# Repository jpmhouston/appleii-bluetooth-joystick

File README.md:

> [!WARNING]
> I'm not really a hardware guy, so there might be stupid stuff here. I assume no liability for you using this with your Apple II. Damage could occur both to it and your ESP32 if I got anything wrong or if you wire it wrong. Build one at your own risk.
> Also, this was built for my Apple IIGS and Laser 128.  They use 9 pin DE9 connectors. You'll have to figure out how to do something different if you have the 15 pin connector.

---

---

# Purpose

My old school analog joystick isn't great so I wanted to buy a "new" one. But I discovered that even crappy period correct ones are like $50 on ebay. I'm cheap and I also have a bunch of modern gamepads around. So I thought, why not build something to allow those modern gamepads to work with my Apple IIGS and my Laser 128?

So this let's you use a modern bluetooth gamepad on an Apple II. I'll probably still buy a joystick, but this was a fun project anyway.

If you do anything with electronics then you probably have a hoard of parts on hand. This project is cheap in theory if you already have common parts like breadboards, resistors, diodes, etc. Most of the components are cheap, but they only come in bulk so you'll end up paying more if you don't already have some on hand. And digikey is great but shipping is $. All in all, depending on what you have hoarded way, it'll probably cost you somewhere between $15 and $35.

Note: I also saw you can buy an A2io. I'm sure it's better, but it was $55 and it looks like it requires using a mobile device. I didn't want to have to use a mobile app and really the fun was in building this.

# Credits

I learned about how the Apple II joysticks work primarily by reading my Laser 128 technical reference manual and [this article](https://blondihacks.com/apple-ii-gamepad-prototype/) by Quinn Dunki.

For the ESP32/bluetooth side, this project uses Bluepad32. Here are some links I found helpful.
* [Some Bluepad32 docs](https://gitlab.com/ricardoquesada/bluepad32/-/blob/main/docs/plat_arduino.md#1-add-esp32-and-bluepad32-board-packages-to-board-manager)
* [ESP-IDF + Arduino + Bluepad32 template app](https://github.com/ricardoquesada/esp-idf-arduino-bluepad32-template)

# Usage

## Connecting everything

Plug the DE9 into your joystick port. Plug your ESP32 into USB. They are powered separately. See the section below on power rails, but generally it should be fine to do this in either order. It's probably a good idea to do this with your Apple off.

## Pairing controllers

By default, bluepad32 pairing is automatic when devices are put in pairing mode. Instead, I implemented an on-device pairing mode so that you can ignore new controllers if you're trying to pair them with other devices in the area. To pair a new controller, you need to bring Pin 13 to low. You can do this with a physical switch or if you're using a breadboard just connect Pin 13 to ground.

If you have one controller connected, then connect another one, the second one will be the one used.

## Calibrating your controller

You may find that center on your joystick isn't center on the Apple II. See the section on how analog sticks work and you can probably guess why. Not to mention you may have decades old capacitors in your machine.

Pressing L1 and R1 simultaneously on your controller will capture an offset value for x and y and apply this to your joystick readings. This allows you to center the controller. If you have the TotalReplay image (google it), there's a joystick program you can use. You can move the stick until it's in the center and press L1 and R1.

The calibration is saved in flash memory so it will stick even when you remove power.

# How this stuff works if you want to build one

As mentioned in the warning at the top of this readme, I know just enough hardware stuff to get by. And not enough to get by in some cases. So if you're reading this and you see I'm wrong about something or did something dangerous, let me know! Especially if there's risk of damaging an Apple II! Better yet, contribute some code or modify the design if you have a better way.

## Analog sticks using digital potentiometers (used as rheostats)

Traditional Apple II analog joysticks were pretty simple. Inside are two 150k ohm potentiometers, one for each axis. As you move the stick, it adjusts the potentiometers (pots) and changes the resistance in a circuit on the Apple II. The computer measures how long it takes to charge an internal capacitor through that resistance. Because the charging time varies, it can detect fine movements and exact angles. This is pretty cool compared to digital joysticks like the C64 or Ataris used, which were simple on-off switches for four directions.

This project works by using digital potentiometers (digipots). It converts the position of the stick on your modern gamepad to resistance values for the digipots. The Apple II expects between 0 and 150kohms resistance but 150kohm resistors are hard to find. So this project uses two 100kohm digipots in series per axis.

If you want to make it cheaper, you can probably just use one 100kohm digipot per axis. You may lose some range, though. I haven't tried this, but it seems like that's what others have done when they've built physical joysticks, and the common complaint is that it may not work great for things like flight simulators.

The code basically sets the two MCP4161 digipots per axis to the same wiper values and wires them in series. E.g. to get 150kohms of resistance, both digipots are set to 75kohm.

Also, my oldschool joystick allowed close to a square movement pattern. My modern gamepads are pretty constrained to a circle. So the code "squares the circle" a bit to provide a more authentic response. You can control how much by tweaking the code. See the SQUARENESS value.

Finally, there are some variables you can set to control how low the wipers can go. Play with those if you want. See WIPER\\_MIN\_SAFE.

## Buttons

Apple II buttons are quite simple. We get the button state from bluepad32. When a button is not being pressed, we want the Apple II button switch input to float. When it's being pressed, we bring it to 5V through a 470 ohm resistor. We make use of a diode for this.

## Power rails

This project interfaces an ESP32 (3.3V logic) with an Apple II (5V logic). Because these devices operate at different voltages, some care was taken to ensure signal integrity and hardware safety. Again, I'm not an expert so please point out any flaws in the design.

## Level shifting, isolation, and fail-safe

All 3.3V SPI and control signals from the ESP32 are level-shifted through a 74HCT245 bus transceiver.
* The 74HCT245 is powered by the 5V rail from the Apple II Game I/O port.
* Note: The "T" variant (HCT) is used because its input threshold is compatible with 3.3V logic but it can output 5V for the Apple II and digipots.

To prevent backfeeding power or sending spurious SPI commands to the digipots when one system is off, the 74HCT245's OE pin is managed by a hardware failsafe.
* A 10K pullup resistor connects the OE pin to the Apple II 5V rail. So if the ESP32 is not connected or is powered down, OE is HIGH and the buffer is in a high impedance state.
* A 2N7000 MOSFET acts as an inverter. When the ESP32 GPIO pins initialize and drive the MOSFET Gate HIGH, the MOSFET pulls the OE pin to ground, enabling the outputs.

Note: The 2N7000 has a gate threshold that can range up to 3.0V. Since the ESP32 outputs 3.3V, there isn't much overhead for the transistor to turn fully on. This should still be sufficient for switching the OE pin, but your mileage may vary. To test, check the voltage at the OE pin. It should drop reasonably close to 0V when the ESP32 is active. A logic-level MOSFET with a lower gate threshold is probably better, but I had a ton of these on hand and it's working for me.

## Parts list

Here's what I used in building this device. It would probably be cheaper to make a PCB since a lot of the expense is breadboards/breakout boards, etc. Most of what I bought came in packs of a bunch, so it could be more expensive if you don't already have stuff on hand like resistors, diodes, etc.
* 1 - [ESP32](https://www.amazon.com/dp/B0D8T53CQ5?ref=ppx_yo2ov_dt_b_fed_asin_title) - $6.67 each. Make sure you get one that supports classic bluetooth mode. Look at bluepad32's docs above to make sure.
* 1 - [ESP32 breakout board](https://www.amazon.com/dp/B0BNQ85GF3?ref=ppx_yo2ov_dt_b_fed_asin_title&th=1) - $4.33 each. Not strictly necessary but made it a lot easier to mess around.
* 4 - [MCP4161-104E/P digipots](https://www.digikey.com/en/products/detail/microchip-technology/MCP4161-104E-P/1874169) - $1.38 each
* 1- [DB9 breakout board] (https://www.amazon.com/dp/B09L7JWNDQ?ref=ppx_yo2ov_dt_b_fed_asin_title&th=1) - $7.96. You can do this with a simple male connector if you want to save money. I just found it a lot easier to wire up this way.
* About 10 [104 capacitors] - about $0.70 total.
* 1- [74HCT245N](https://www.digikey.com/en/products/detail/texas-instruments/SN74HCT245N/277258) - $0.92 each.
* 2 - 1N5817 diodes
* 1 - [2N7000 MOSFET](https://www.amazon.com/dp/B0CBKHJQZF?ref=ppx_yo2ov_dt_b_fed_asin_title&th=1) - $0.08 each. 
* Resistors. Just get a kit if you don't already have any. You'll need 6x1kohm resistors, a couple of 10K resistors, a couple of 470ohm resistors.
* Wire and terminals depending on how you want to build it.
* Breadboard or a solderable board of some kind.. Get whatever you want. A good one's about $8.

## Layout

Check out the [schematic](./schematic/schematic.kicad_sch) built using [KiCad](https://www.kicad.org/). 

Notes:
* My ESP32 had different pin numbers than the drawing shows, so just make sure the right GPIO/IO lines are used rather than paying attention to the pin numbers listed.
* I also sprinkled some 0.1 µF ceramic capacitors (104s) along the power rails (VCC to GND). These aren't shown in the drawing.
* The Apple II calls for 470ohm resistors on the buttons. On my Laser 128, that kept me borderline on button presses. I DON'T RECOMMEND IT BECAUSE THE SPEC CALLS FOR 470 ohms and I'm paranoid. But if the buttons aren't triggering you could try a lower value resistor. Do this at your own risk.

# Next steps / Possible problems

It might be good to add some physical pots for the stick calibration. Some adjustments for min/max resistance and for centering. We could get much more precise calibrations that way and you wouldn't need to use a calibration program. You could also do it mid-game.

I noticed that when you have the stick all the way down and to the left, sometimes there's an overflow and the stick will jump to the top in the joystick calibration program. This also happens with my old school physical joystick so maybe it's just a practical hardware limitation.

I've never designed a PCB before, but I think this would be pretty cheap if someone wanted to give it a go. I'd go in on it with you if you want to build a bunch. I used through hole components since I suck at soldering and am scared to try doing SMDs.

---

# Addendum by jpmhouston ... Second draft of a PCB 🎉

This is made directly from the KiCad schematic, I haven't made a breadboard prototype yet. I'm a beginner at PCBs also, but started learning KiCad recently for another project.

I don't know much about the DE9 serial port connector and its mounting screws (called jackscrews?), but I moved some components around from the simply rectangular, first draft PCB and now there might be enough space for them (slightly more then 1cm).

Component Q3 is the one I didn't find a surface mount replacement for however there's more than enough vertical space for it compared to the DE9 connector which I placed it close to. I picked a push button for the pairing switch and placed it at the back. The only thinking I did about a case is guessing that it could be made shallow at the back to allow exposing this button.

I also don't know much about the ESP32 and guessed that the antenna part needs to be exposed off the board at the back, exposed though an eventual case.

This board design measures 34mm wide (just under 1 3/8") x 35.8mm deep (also roughly 1 1/2") not counting the antenna. I haven't yet, but I intended to make a mock up out of cardboard, see how this sizes up compared to real hardware (I have a //e here).

---

These are the changes made to KiCad schematic, mostly just finding replacement surface mount components but I did make changes to the symbols for the diode and DE9 connector. I'm hoping kirbyfrugia can give it a look before I do a pull request, an exported png of the schematic is in "images/kicad schematic update.png". Also FYI, some of the component choices were made with assistance from an LLM, they need to be reviewed by knowledgeable human.

```
Renumbered U1-5 to make MCP4161's U1-4 corresponding to C1-4, ESP now U5
Renumbered R5,6 to R3,4 as schematic had no R3,4

Added model to ESP32 U5:

same data sheet, symbol, footprint
files from https://www.digikey.com/en/products/detail/espressif-systems/ESP32-WROOM-32E-N8/13159522 (saved to components/ESP32-WROOM-32E)
3d model ${KIPRJMOD}/components/ESP32-WROOM-32E/ESP32-WROOM-32E-N8.STEP (x: 90deg, dy: 3.0mm)

Picked replacement surface mount parts for MCP4161 U1-4:

same data sheet and symbol, new footprint and 3d model
files from https://www.digikey.com/en/products/detail/microchip-technology/MCP4161-104E-MS/1874189 (saved to components/MCP4161_104E_MS)
footprint MCP4161_104E_MS:MSOP8_MC_MCH after adding ${KIPRJMOD}/components/MCP4161_104E_MS/KiCADv6/footprints.pretty
3d model ${KIPRJMOD}/components/MCP4161_104E_MS/MSOP8_MC_MCH.step

Picked replacement surface mount part for U6:

same data sheet and symbol, new footprint and 3d model
files from https://www.digikey.com/en/products/detail/texas-instruments/SN74HCT245DW/277257 (saved to components/SN74HCT245DW)
footprint SN74HCT245DW:DW20 after adding ${KIPRJMOD}/components/SN74HCT245DW/KiCADv6/footprints.pretty
3d model ${KIPRJMOD}/components/SN74HCT245DW/DW0020A.stp

Changed JS1 to a true DE9 symbol, footprint, model:

new symbol 9-pin D-SUB connector, pins (male), Mounting Hole
footprint Connector_Dsub:DSUB-9_Pins_Horizontal_P2.77x2.54mm_EdgePinOffset9.40mm

Picked surface mount part for switch SW1:

same symbol, new data sheet, footprint and 3d model
Omron B3U-1000P-B data sheet https://omronfs.omron.com/en_US/ecb/products/pdf/en-b3u.pdf
files from https://www.digikey.com/en/products/detail/omron-electronics-inc-emc-div/B3U-1000P-B/1811777 (saved to components/B3U_1000P_B)
footprint B3U_1000P_B:B3U-1000P-B after adding ${KIPRJMOD}/components/B3U_1000P_B/KiCADv6/footprints.pretty
3d model ${KIPRJMOD}/components/B3U_1000P_B/B3U_1000P[]_B.step (x: 90deg)

Picked surface mount parts for resistors R1-4:

same symbol, new footprint and 3d model
https://pim.murata.com/asset/pim4/ceramicCapacitorSMD/GRM188D71A475KE11-01A-EN_PDF_CERAMICCAPACITORSMD
footprint Resistor_SMD:R_0603_1608Metric_Pad0.98x0.95mm_HandSolder
3d model ${KICAD9_3DMODEL_DIR}/Resistor_SMD.3dshapes/R_0603_1608Metric.step

Picked surface mount parts for capacitors C1-4:

same symbol, new footprint and 3d model
https://yageogroup.com/content/Resource%20Library/Datasheet/PYU-RC_51_ROHS_P.pdf
footprint Capacitor_SMD:C_0603_1608Metric_Pad1.08x0.95mm_HandSolder
3m model ${KICAD9_3DMODEL_DIR}/Capacitor_SMD.3dshapes/C_0603_1608Metric.step

Changed D1,2 barrier rectifier diodes to D1 single surface mount package containing 2 independent barrier rectifiers:

new symbol, footprint, 3d model
Diode Array 2 Independent 20 V 1A Surface Mount SOT-23-5 Thin, TSOT-23-5
data sheet https://fscdn.rohm.com/en/products/databook/datasheet/discrete/diode/schottky_barrier/rb496eatr-e.pdf
files from https://www.digikey.ca/en/models/926235 (saved to components/RB496EATR)
symbol RB496EATR after adding symbol ${KIPRJMOD}/components/RB496EATR/KiCADv6/2026-03-08_05-44-21.kicad_sym
footprint RB496EATR:DIO_FTZ_ROM after adding ${KIPRJMOD}/components/RB496EATR/KiCADv6/footprints.pretty
3d model ${KIPRJMOD}/components/RB496EATR/DIO_FTZ_ROM.step
```

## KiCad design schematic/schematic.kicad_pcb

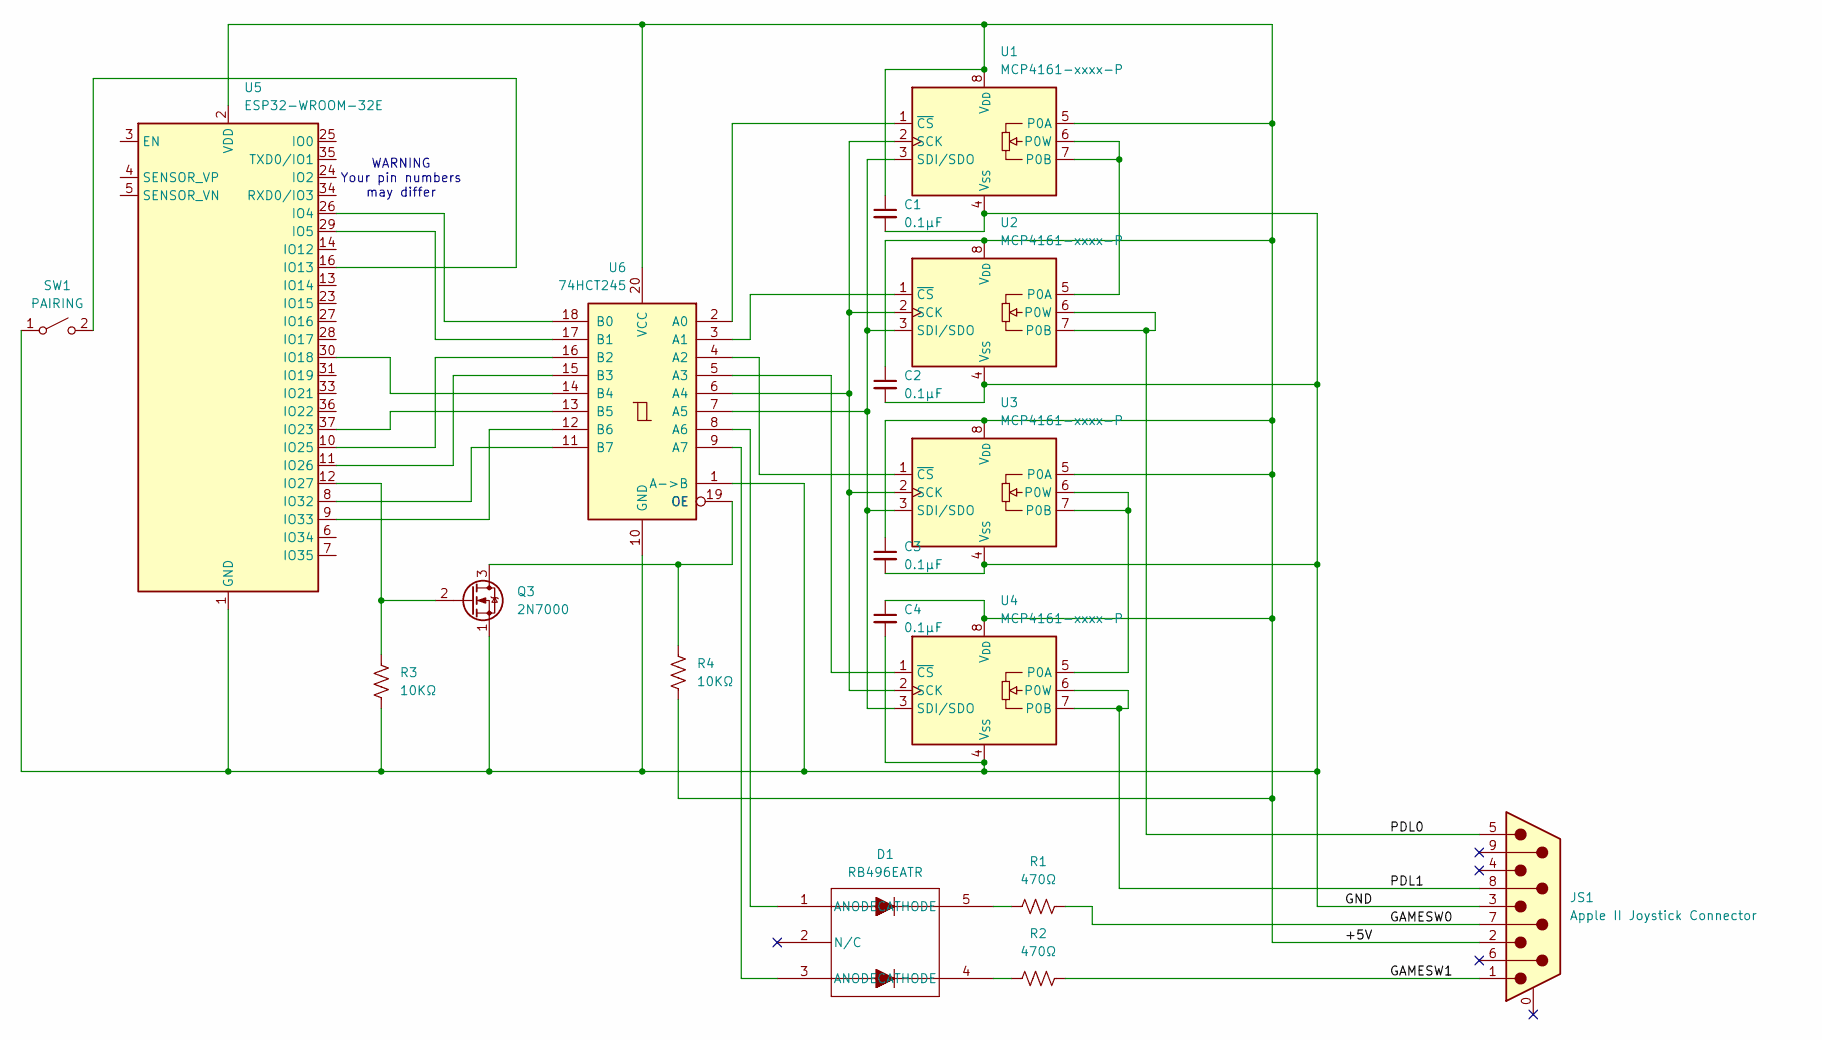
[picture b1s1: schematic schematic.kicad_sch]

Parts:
C1, C2, C3, C4: 0.1µF; C_0603_1608Metric_Pad1.08x0.95mm_HandSolder
D1: RB496EATR; DIO_FTZ_ROM
JS1: Apple II Joystick Connector; DSUB-9_Pins_Horizontal_P2.77x2.54mm_EdgePinOffset9.40mm
Q3: 2N7000; TO-92_Inline
R1, R2: 470Ω; R_0603_1608Metric_Pad0.98x0.95mm_HandSolder
R3, R4: 10KΩ; R_0603_1608Metric_Pad0.98x0.95mm_HandSolder
SW1: PAIRING; B3U-1000P-B
U1, U2, U3, U4: MCP4161-xxxx-P; MSOP8_MC_MCH
U5: ESP32-WROOM-32E; ESP32-WROOM-32D
U6: 74HCT245; DW20

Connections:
/+5V: C1.1, C2.1, C3.1, C4.1, JS1.2, R4.2, U1.5 (P0A), U1.8 (V_{DD}), U2.8 (V_{DD}), U3.5 (P0A), U3.8 (V_{DD}), U4.8 (V_{DD}), U5.2 (VDD), U6.20 (VCC)
/GAMESW0: JS1.7, R1.2
/GAMESW1: JS1.1, R2.2
/GND: C1.2, C2.2, C3.2, C4.2, JS1.3, Q3.1 (S), R3.2, SW1.1 (A), U1.4 (V_{SS}), U2.4 (V_{SS}), U3.4 (V_{SS}), U4.4 (V_{SS}), U5.1 (GND), U5.15 (GND), U5.38 (GND), U5.39 (GND), U6.1 (A->B), U6.10 (GND)
/PDL0: JS1.5, U2.6 (P0W), U2.7 (P0B)
/PDL1: JS1.8, U4.6 (P0W), U4.7 (P0B)
unnamed: D1.4 (CATHODE), R2.1
unnamed: D1.5 (CATHODE), R1.1
unnamed: Q3.3 (D), R4.1, U6.19 (CE)
unnamed: Q3.2 (G), R3.1, U5.12 (IO27)
unnamed: SW1.2 (B), U5.16 (IO13)
unnamed: U1.6 (P0W), U1.7 (P0B), U2.5 (P0A)
unnamed: U1.2 (SCK), U2.2 (SCK), U3.2 (SCK), U4.2 (SCK), U6.6 (A4)
unnamed: U1.3 (SDI/SDO), U2.3 (SDI/SDO), U3.3 (SDI/SDO), U4.3 (SDI/SDO), U6.7 (A5)
unnamed: U1.1 (~CS), U6.2 (A0)
unnamed: U2.1 (~CS), U6.3 (A1)
unnamed: U3.6 (P0W), U3.7 (P0B), U4.5 (P0A)
unnamed: U3.1 (~CS), U6.4 (A2)
unnamed: U4.1 (~CS), U6.5 (A3)
unnamed: U5.26 (IO4), U6.18 (B0)
unnamed: U5.29 (IO5), U6.17 (B1)
unnamed: U5.30 (IO18), U6.14 (B4)
unnamed: U5.37 (IO23), U6.13 (B5)
unnamed: U5.10 (IO25), U6.16 (B2)
unnamed: U5.11 (IO26), U6.15 (B3)
unnamed: U5.8 (IO32), U6.11 (B7)
unnamed: U5.9 (IO33), U6.12 (B6)
unnamed: D1.1 (ANODE), U6.8 (A6)
unnamed: D1.3 (ANODE), U6.9 (A7)

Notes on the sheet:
WARNING Your pin numbers may differ

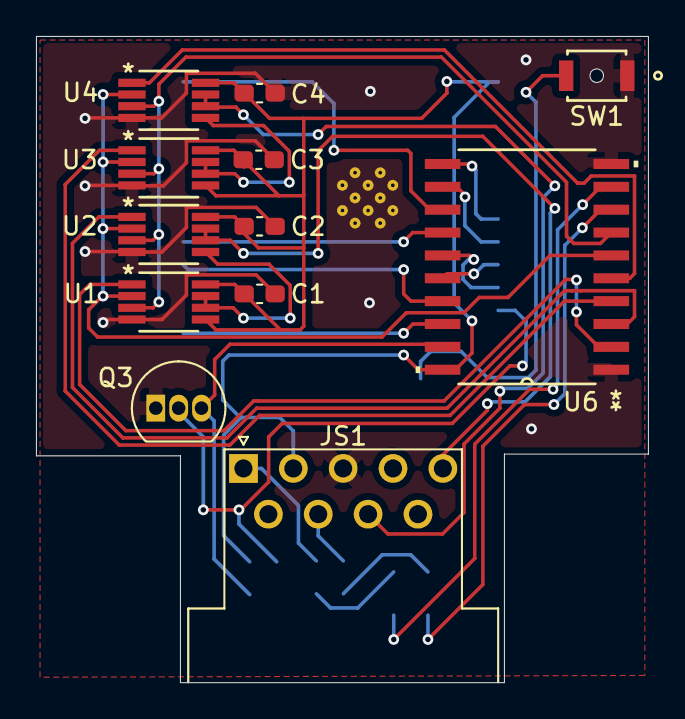
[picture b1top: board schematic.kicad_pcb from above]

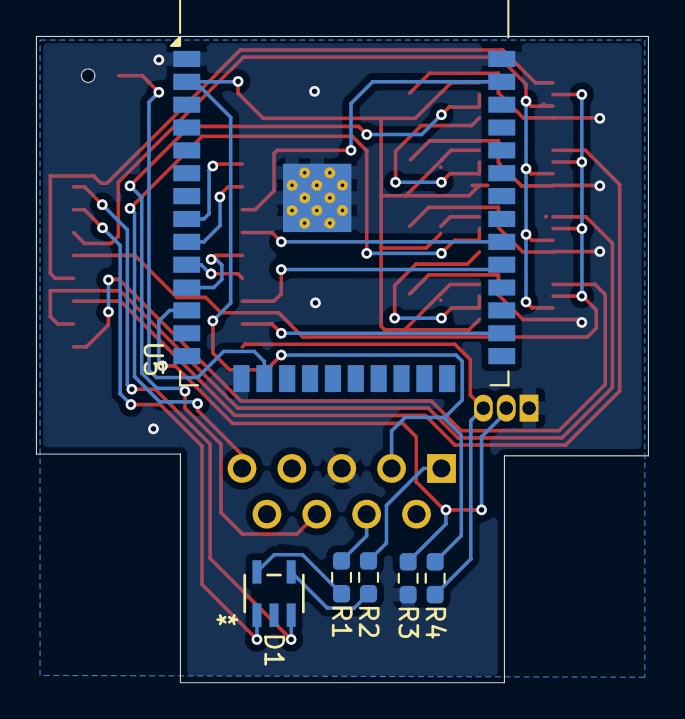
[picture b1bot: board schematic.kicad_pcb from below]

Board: 2 copper layers, 34.0 x 35.9 mm, 18 parts (6 on the bottom side), 29 nets.

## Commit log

2026-03-08 pcb first draft
    minor changes to the schematic: DE9 connector symbol, the 2 separate diodes changed to one component
2026-03-08 prev commit described in readme addendum
2026-04-26 maybe fixed caps, made space for de9 jackscrews
